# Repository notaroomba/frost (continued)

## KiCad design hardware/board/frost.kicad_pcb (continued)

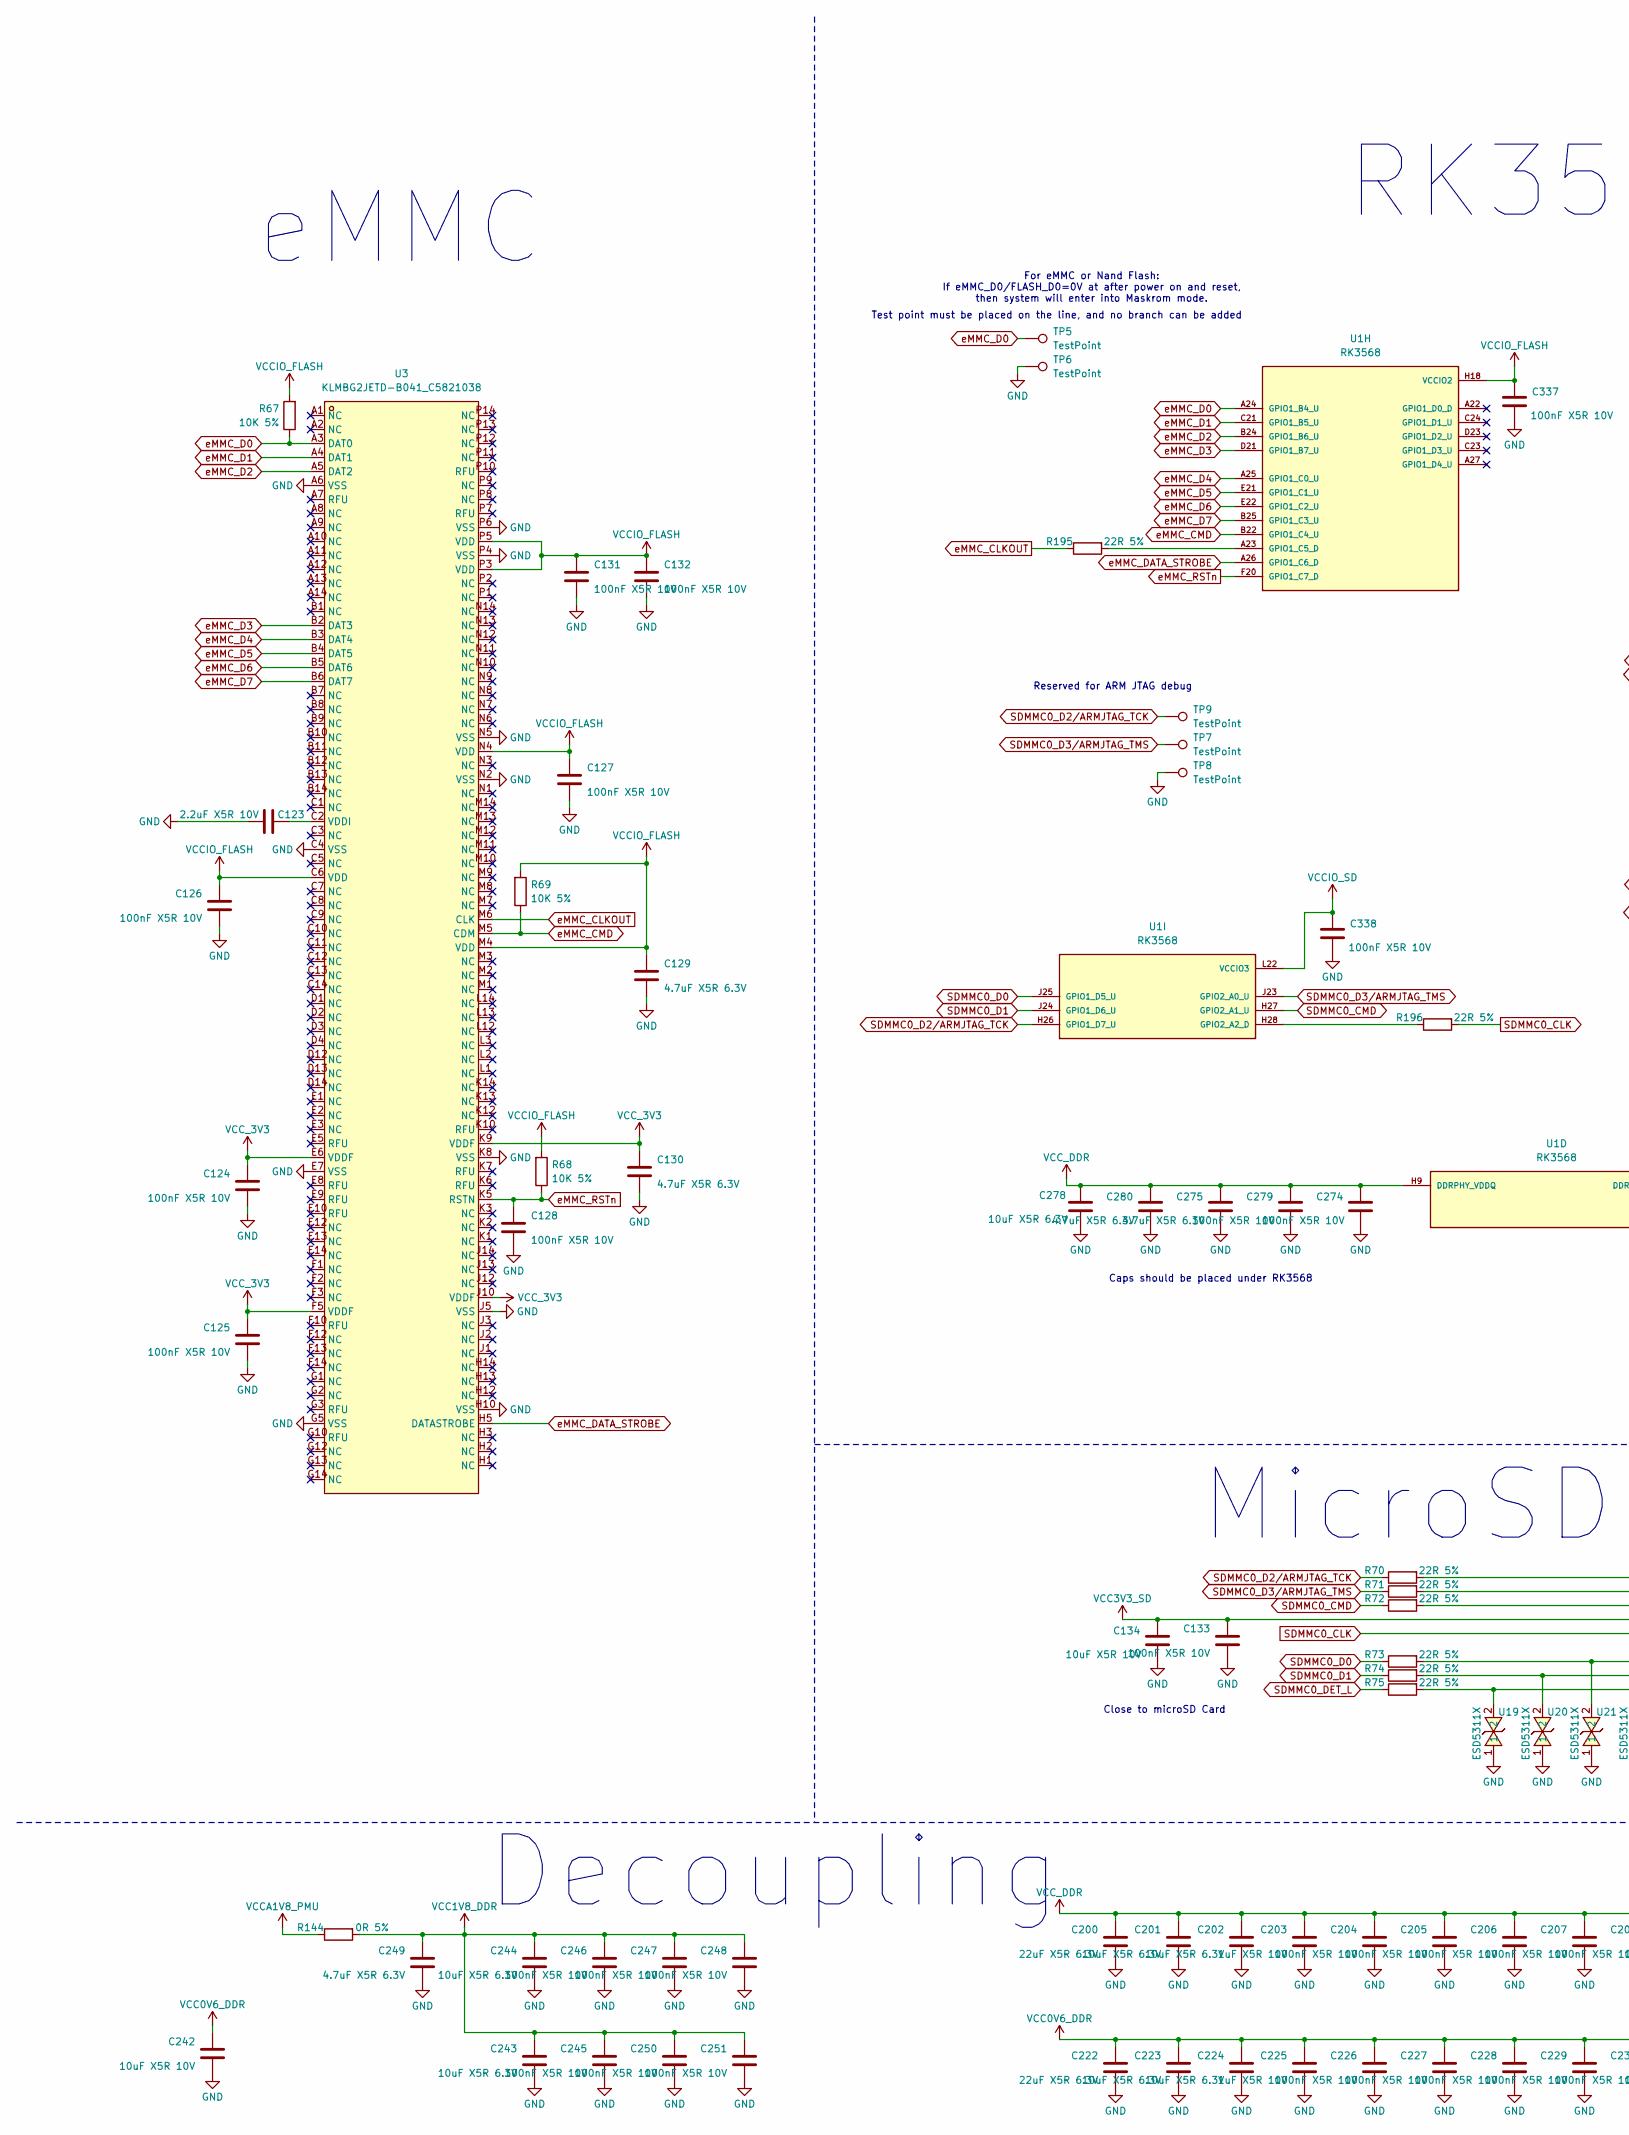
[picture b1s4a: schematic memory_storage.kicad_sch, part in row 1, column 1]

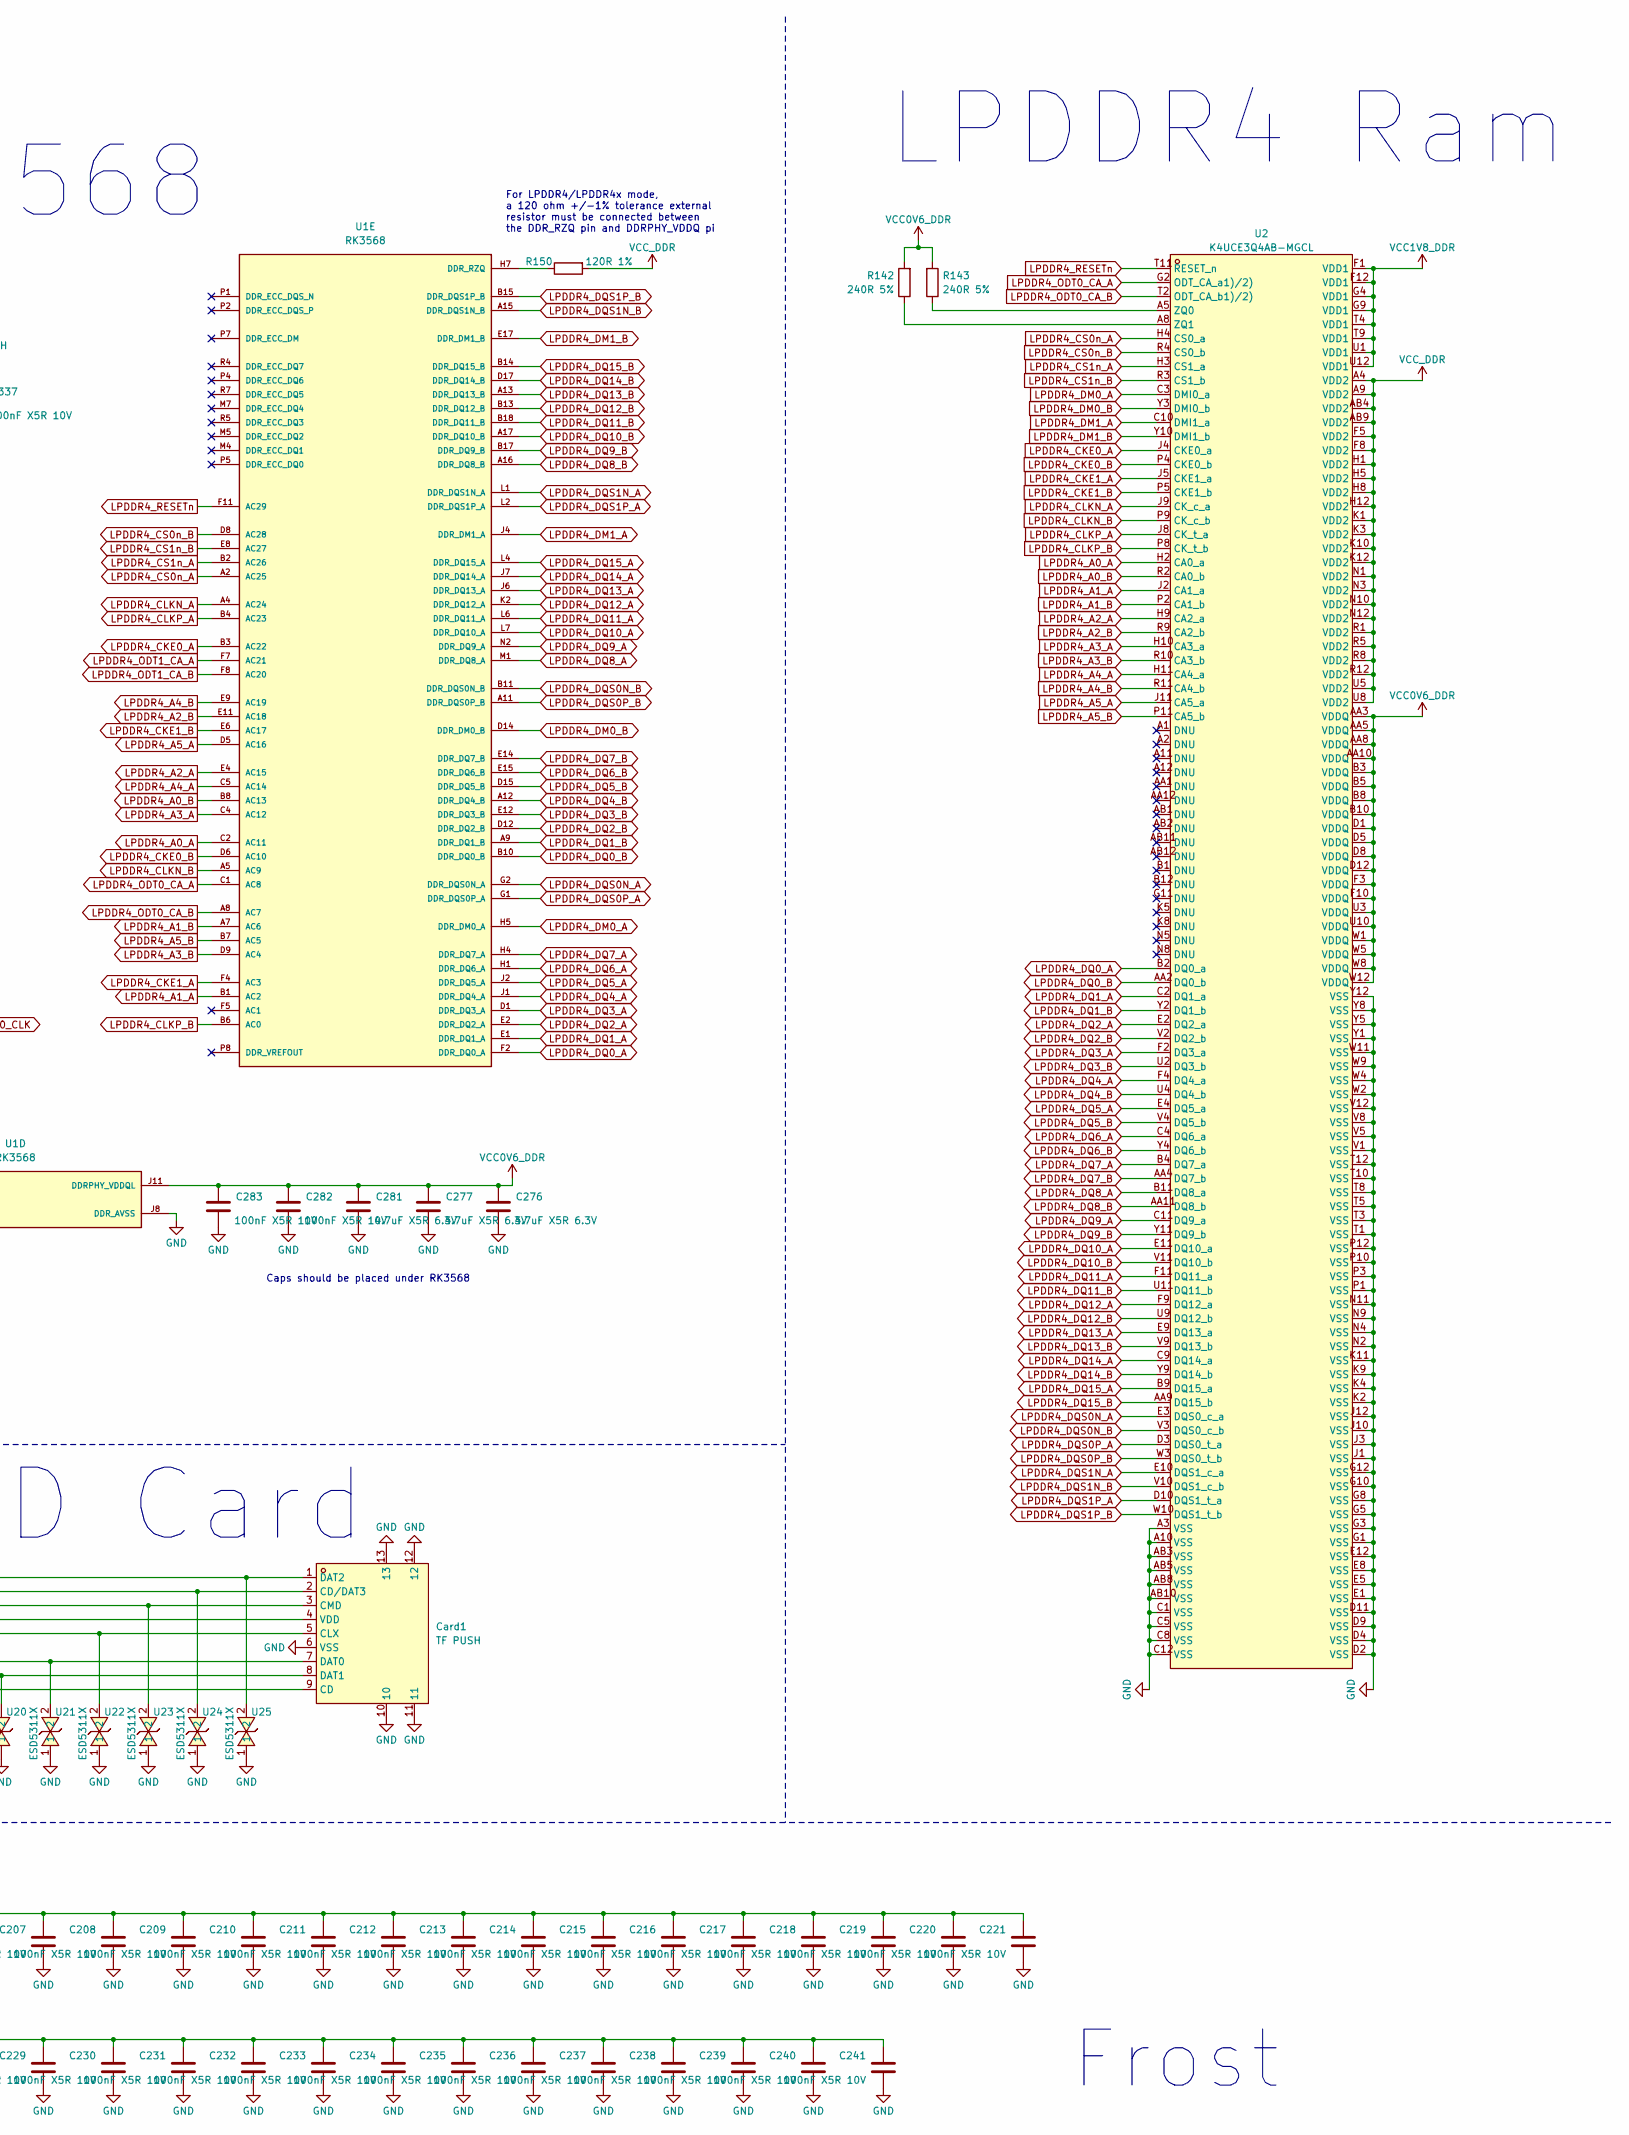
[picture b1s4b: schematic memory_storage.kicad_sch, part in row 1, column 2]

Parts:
C123: 2.2uF X5R 10V; C_0402_1005Metric
C124, C125, C126, C127, C128, C131, C132, C133, C204, C205, C206, C207, C208, C209, C210, C211, C212, C213, C214, C215, C216, C217, C218, C219, C220, C221, C226, C227, C228, C229, C230, C231, C232, C233, C234, C235, C236, C237, C238, C239, C240, C241, C245, C246, C247, C248, C250, C251: 100nF X5R 10V; C_0402_1005Metric
C129, C130: 4.7uF X5R 6.3V; C_0603_1608Metric
C134, C242: 10uF X5R 10V; C_0603_1608Metric
C200, C222: 22uF X5R 6.3V; C_0603_1608Metric
C201, C202, C223, C224, C243, C244, C278: 10uF X5R 6.3V; C_0603_1608Metric
C203, C225: 1uF X5R 10V; C_0402_1005Metric
C249, C275, C276, C277, C280, C281: 4.7uF X5R 6.3V; C_0402_1005Metric
C274, C279, C282, C283, C337, C338: 100nF X5R 10V; C_0201_0603Metric
Card1: TF PUSH; TF-SMD_TF-PUSH; LCSC Part C393941
R67, R68, R69: 10K 5%; R_0402_1005Metric
R70, R71, R72, R73, R74, R75, R195, R196: 22R 5%; R_0402_1005Metric
R142, R143: 240R 5%; R_0402_1005Metric
R144: 0R 5%; R_0201_0603Metric
R150: 120R 1%; R_0201_0603Metric
TP5, TP6, TP7, TP8, TP9: TestPoint; TestPoint_Pad_D1.0mm
U1: RK3568; BGA636C65P28X28_1900X1900X168; PARTREV 1.3; LCSC C3345225
U2: K4UCE3Q4AB-MGCL; FBGA-200_L15.0-W10.0-BL_RS512M32LO4D1BDS-53BT; LCSC Part C29073172
U3: KLMBG2JETD-B041_C5821038; BGA-153_L13.0-W11.5-P0.50-TL_KLM8G1GEME-B041; LCSC Part C5821038
U19, U20, U21, U22, U23, U24, U25: ESD5311X; DFN1006-2L-BI; LCSC Part C2844730

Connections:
LPDDR4_A0_A: U1.C2 (AC11), U2.H2 (CA0_a)
LPDDR4_A0_B: U1.B8 (AC13), U2.R2 (CA0_b)
LPDDR4_A1_A: U1.B1 (AC2), U2.J2 (CA1_a)
LPDDR4_A1_B: U1.A7 (AC6), U2.P2 (CA1_b)
LPDDR4_A2_A: U1.E4 (AC15), U2.H9 (CA2_a)
LPDDR4_A2_B: U1.E11 (AC18), U2.R9 (CA2_b)
LPDDR4_A3_A: U1.C4 (AC12), U2.H10 (CA3_a)
LPDDR4_A3_B: U1.D9 (AC4), U2.R10 (CA3_b)
LPDDR4_A4_A: U1.C5 (AC14), U2.H11 (CA4_a)
LPDDR4_A4_B: U1.E9 (AC19), U2.R11 (CA4_b)
LPDDR4_A5_A: U1.D5 (AC16), U2.J11 (CA5_a)
LPDDR4_A5_B: U1.B7 (AC5), U2.P11 (CA5_b)
LPDDR4_CKE0_A: U1.B3 (AC22), U2.J4 (CKE0_a)
LPDDR4_CKE0_B: U1.D6 (AC10), U2.P4 (CKE0_b)
LPDDR4_CKE1_A: U1.F4 (AC3), U2.J5 (CKE1_a)
LPDDR4_CKE1_B: U1.E6 (AC17), U2.P5 (CKE1_b)
LPDDR4_CLKN_A: U1.A4 (AC24), U2.J9 (CK_c_a)
LPDDR4_CLKN_B: U1.A5 (AC9), U2.P9 (CK_c_b)
LPDDR4_CLKP_A: U1.B4 (AC23), U2.J8 (CK_t_a)
LPDDR4_CLKP_B: U1.B6 (AC0), U2.P8 (CK_t_b)
LPDDR4_CS0n_A: U1.A2 (AC25), U2.H4 (CS0_a)
LPDDR4_CS0n_B: U1.D8 (AC28), U2.R4 (CS0_b)
LPDDR4_CS1n_A: U1.B2 (AC26), U2.H3 (CS1_a)
LPDDR4_CS1n_B: U1.E8 (AC27), U2.R3 (CS1_b)
LPDDR4_DM0_A: U1.H5 (DDR_DM0_A), U2.C3 (DMI0_a)
LPDDR4_DM0_B: U1.D14 (DDR_DM0_B), U2.Y3 (DMI0_b)
LPDDR4_DM1_A: U1.J4 (DDR_DM1_A), U2.C10 (DMI1_a)
LPDDR4_DM1_B: U1.E17 (DDR_DM1_B), U2.Y10 (DMI1_b)
LPDDR4_DQ0_A: U1.F2 (DDR_DQ0_A), U2.B2 (DQ0_a)
LPDDR4_DQ0_B: U1.B10 (DDR_DQ0_B), U2.AA2 (DQ0_b)
LPDDR4_DQ1_A: U1.E1 (DDR_DQ1_A), U2.C2 (DQ1_a)
LPDDR4_DQ1_B: U1.A9 (DDR_DQ1_B), U2.Y2 (DQ1_b)
LPDDR4_DQ2_A: U1.E2 (DDR_DQ2_A), U2.E2 (DQ2_a)
LPDDR4_DQ2_B: U1.D12 (DDR_DQ2_B), U2.V2 (DQ2_b)
LPDDR4_DQ3_A: U1.D1 (DDR_DQ3_A), U2.F2 (DQ3_a)
LPDDR4_DQ3_B: U1.E12 (DDR_DQ3_B), U2.U2 (DQ3_b)
LPDDR4_DQ4_A: U1.J1 (DDR_DQ4_A), U2.F4 (DQ4_a)
LPDDR4_DQ4_B: U1.A12 (DDR_DQ4_B), U2.U4 (DQ4_b)
LPDDR4_DQ5_A: U1.J2 (DDR_DQ5_A), U2.E4 (DQ5_a)
LPDDR4_DQ5_B: U1.D15 (DDR_DQ5_B), U2.V4 (DQ5_b)
LPDDR4_DQ6_A: U1.H1 (DDR_DQ6_A), U2.C4 (DQ6_a)
LPDDR4_DQ6_B: U1.E15 (DDR_DQ6_B), U2.Y4 (DQ6_b)
LPDDR4_DQ7_A: U1.H4 (DDR_DQ7_A), U2.B4 (DQ7_a)
LPDDR4_DQ7_B: U1.E14 (DDR_DQ7_B), U2.AA4 (DQ7_b)
LPDDR4_DQ8_A: U1.M1 (DDR_DQ8_A), U2.B11 (DQ8_a)
LPDDR4_DQ8_B: U1.A16 (DDR_DQ8_B), U2.AA11 (DQ8_b)
LPDDR4_DQ9_A: U1.N2 (DDR_DQ9_A), U2.C11 (DQ9_a)
LPDDR4_DQ9_B: U1.B17 (DDR_DQ9_B), U2.Y11 (DQ9_b)
LPDDR4_DQ10_A: U1.L7 (DDR_DQ10_A), U2.E11 (DQ10_a)
LPDDR4_DQ10_B: U1.A17 (DDR_DQ10_B), U2.V11 (DQ10_b)
LPDDR4_DQ11_A: U1.L6 (DDR_DQ11_A), U2.F11 (DQ11_a)
LPDDR4_DQ11_B: U1.B18 (DDR_DQ11_B), U2.U11 (DQ11_b)
LPDDR4_DQ12_A: U1.K2 (DDR_DQ12_A), U2.F9 (DQ12_a)
LPDDR4_DQ12_B: U1.B13 (DDR_DQ12_B), U2.U9 (DQ12_b)
LPDDR4_DQ13_A: U1.J6 (DDR_DQ13_A), U2.E9 (DQ13_a)
LPDDR4_DQ13_B: U1.A13 (DDR_DQ13_B), U2.V9 (DQ13_b)
LPDDR4_DQ14_A: U1.J7 (DDR_DQ14_A), U2.C9 (DQ14_a)
LPDDR4_DQ14_B: U1.D17 (DDR_DQ14_B), U2.Y9 (DQ14_b)
LPDDR4_DQ15_A: U1.L4 (DDR_DQ15_A), U2.B9 (DQ15_a)
LPDDR4_DQ15_B: U1.B14 (DDR_DQ15_B), U2.AA9 (DQ15_b)
LPDDR4_DQS0N_A: U1.G2 (DDR_DQS0N_A), U2.E3 (DQS0_c_a)
LPDDR4_DQS0N_B: U1.B11 (DDR_DQS0N_B), U2.V3 (DQS0_c_b)
LPDDR4_DQS0P_A: U1.G1 (DDR_DQS0P_A), U2.D3 (DQS0_t_a)
LPDDR4_DQS0P_B: U1.A11 (DDR_DQS0P_B), U2.W3 (DQS0_t_b)
LPDDR4_DQS1N_A: U1.L1 (DDR_DQS1N_A), U2.E10 (DQS1_c_a)
LPDDR4_DQS1N_B: U1.A15 (DDR_DQS1N_B), U2.V10 (DQS1_c_b)
LPDDR4_DQS1P_A: U1.L2 (DDR_DQS1P_A), U2.D10 (DQS1_t_a)
LPDDR4_DQS1P_B: U1.B15 (DDR_DQS1P_B), U2.W10 (DQS1_t_b)
LPDDR4_ODT0_CA_A: U1.C1 (AC8), U2.G2 (ODT_CA_a1)/2))
LPDDR4_ODT0_CA_B: U1.A8 (AC7), U2.T2 (ODT_CA_b1)/2))
LPDDR4_ODT1_CA_A: U1.F7 (AC21)
LPDDR4_ODT1_CA_B: U1.F8 (AC20)
LPDDR4_RESETn: U1.F11 (AC29), U2.T11 (RESET_n)
unnamed: Card1.9 (CD), R75.2, U19.2
unnamed: Card1.2 (CD/DAT3), R71.2, U24.2
unnamed: Card1.3 (CMD), R72.2, U23.2
unnamed: Card1.7 (DAT0), R73.2, U21.2
unnamed: Card1.8 (DAT1), R74.2, U20.2
unnamed: Card1.1 (DAT2), R70.2, U25.2
unnamed: R150.1, U1.H7 (DDR_RZQ)
unnamed: R195.2, U1.A23 (GPIO1_C5_D)
unnamed: R196.1, U1.H28 (GPIO2_A2_D)
unnamed: R143.1, U2.A5 (ZQ0)
unnamed: R142.1, U2.A8 (ZQ1)
unnamed: C123.1, U3.C2 (VDDI)
SDMMC0_CLK: Card1.5 (CLX), R196.2, U22.2
SDMMC0_CMD: R72.1, U1.H27 (GPIO2_A1_U)
SDMMC0_D0: R73.1, U1.J25 (GPIO1_D5_U)
SDMMC0_D1: R74.1, U1.J24 (GPIO1_D6_U)
SDMMC0_D2/ARMJTAG_TCK: R70.1, TP9.1, U1.H26 (GPIO1_D7_U)
SDMMC0_D3/ARMJTAG_TMS: R71.1, TP7.1, U1.J23 (GPIO2_A0_U)
SDMMC0_DET_L: R75.1; also elsewhere on the board
VCC0V6_DDR: C222.1, C223.1, C224.1, C225.1, C226.1, C227.1, C228.1, C229.1, C230.1, C231.1, C232.1, C233.1, C234.1, C235.1, C236.1, C237.1, C238.1, C239.1, C240.1, C241.1, C242.1, C276.1, C277.1, C281.1, C282.1, C283.1, R142.2, R143.2, U1.J11 (DDRPHY_VDDQL), U1.J12 (DDRPHY_VDDQL), U1.J14 (DDRPHY_VDDQL), U1.K10 (DDRPHY_VDDQL), U1.L10 (DDRPHY_VDDQL), U1.M10 (DDRPHY_VDDQL), U2.AA3 (VDDQ), U2.AA5 (VDDQ), U2.AA8 (VDDQ), U2.AA10 (VDDQ), U2.B3 (VDDQ), U2.B5 (VDDQ), U2.B8 (VDDQ), U2.B10 (VDDQ), U2.D1 (VDDQ), U2.D5 (VDDQ), U2.D8 (VDDQ), U2.D12 (VDDQ), U2.F3 (VDDQ), U2.F10 (VDDQ), U2.U3 (VDDQ), U2.U10 (VDDQ), U2.W1 (VDDQ), U2.W5 (VDDQ), U2.W8 (VDDQ), U2.W12 (VDDQ)
VCC1V8_DDR: C243.1, C244.1, C245.1, C246.1, C247.1, C248.1, C249.1, C250.1, C251.1, R144.2, U2.F1 (VDD1), U2.F12 (VDD1), U2.G4 (VDD1), U2.G9 (VDD1), U2.T4 (VDD1), U2.T9 (VDD1), U2.U1 (VDD1), U2.U12 (VDD1)
VCC3V3_SD: C133.1, C134.1, Card1.4 (VDD); also elsewhere on the board
VCCA1V8_PMU: R144.1; also elsewhere on the board
VCCIO_FLASH: C126.1, C127.1, C129.1, C131.1, C132.1, C337.1, R67.2, R68.2, R69.2, U1.H18 (VCCIO2), U3.C6 (VDD), U3.M4 (VDD), U3.N4 (VDD), U3.P3 (VDD), U3.P5 (VDD); also elsewhere on the board
VCCIO_SD: C338.1, U1.L22 (VCCIO3); also elsewhere on the board
VCC_3V3: C124.1, C125.1, C130.1, U3.E6 (VDDF), U3.F5 (VDDF), U3.J10 (VDDF), U3.K9 (VDDF); also elsewhere on the board
VCC_DDR: C200.1, C201.1, C202.1, C203.1, C204.1, C205.1, C206.1, C207.1, C208.1, C209.1, C210.1, C211.1, C212.1, C213.1, C214.1, C215.1, C216.1, C217.1, C218.1, C219.1, C220.1, C221.1, C274.1, C275.1, C278.1, C279.1, C280.1, R150.2, U1.H9 (DDRPHY_VDDQ), U1.H11 (DDRPHY_VDDQ), U1.H12 (DDRPHY_VDDQ), U1.H14 (DDRPHY_VDDQ), U1.H15 (DDRPHY_VDDQ), U1.J9 (DDRPHY_VDDQ), U1.L9 (DDRPHY_VDDQ), U1.M9 (DDRPHY_VDDQ), U2.A4 (VDD2), U2.A9 (VDD2), U2.AB4 (VDD2), U2.AB9 (VDD2), U2.F5 (VDD2), U2.F8 (VDD2), U2.H1 (VDD2), U2.H5 (VDD2), U2.H8 (VDD2), U2.H12 (VDD2), U2.K1 (VDD2), U2.K3 (VDD2), U2.K10 (VDD2), U2.K12 (VDD2), U2.N1 (VDD2), U2.N3 (VDD2), U2.N10 (VDD2), U2.N12 (VDD2), U2.R1 (VDD2), U2.R5 (VDD2), U2.R8 (VDD2), U2.R12 (VDD2), U2.U5 (VDD2), U2.U8 (VDD2); also elsewhere on the board
eMMC_CLKOUT: R195.1, U3.M6 (CLK)
eMMC_CMD: R69.1, U1.B22 (GPIO1_C4_U), U3.M5 (CDM)
eMMC_D0: R67.1, TP5.1, U1.A24 (GPIO1_B4_U), U3.A3 (DAT0)
eMMC_D1: U1.C21 (GPIO1_B5_U), U3.A4 (DAT1)
eMMC_D2: U1.B24 (GPIO1_B6_U), U3.A5 (DAT2)
eMMC_D3: U1.D21 (GPIO1_B7_U), U3.B2 (DAT3)
eMMC_D4: U1.A25 (GPIO1_C0_U), U3.B3 (DAT4)
eMMC_D5: U1.E21 (GPIO1_C1_U), U3.B4 (DAT5)
eMMC_D6: U1.E22 (GPIO1_C2_U), U3.B5 (DAT6)
eMMC_D7: U1.B25 (GPIO1_C3_U), U3.B6 (DAT7)
eMMC_DATA_STROBE: U1.A26 (GPIO1_C6_D), U3.H5 (DATASTROBE)
eMMC_RSTn: C128.1, R68.1, U1.F20 (GPIO1_C7_D), U3.K5 (RSTN)

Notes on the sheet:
Caps should be placed under RK3568
Test point must be placed on the line, and no branch can be added
LPDDR4 Ram
Reserved for ARM JTAG debug
Close to microSD Card
Decoupling
For LPDDR4/LPDDR4x mode, a 120 ohm +/-1% tolerance external resistor must be connected between the DDR_RZQ pin and DDRPHY_VDDQ pi
For eMMC or Nand Flash: If eMMC_D0/FLASH_D0=0V at after power on and reset, then system will enter into Maskrom mode.
eMMC
MicroSD Card
Frost
RK3568

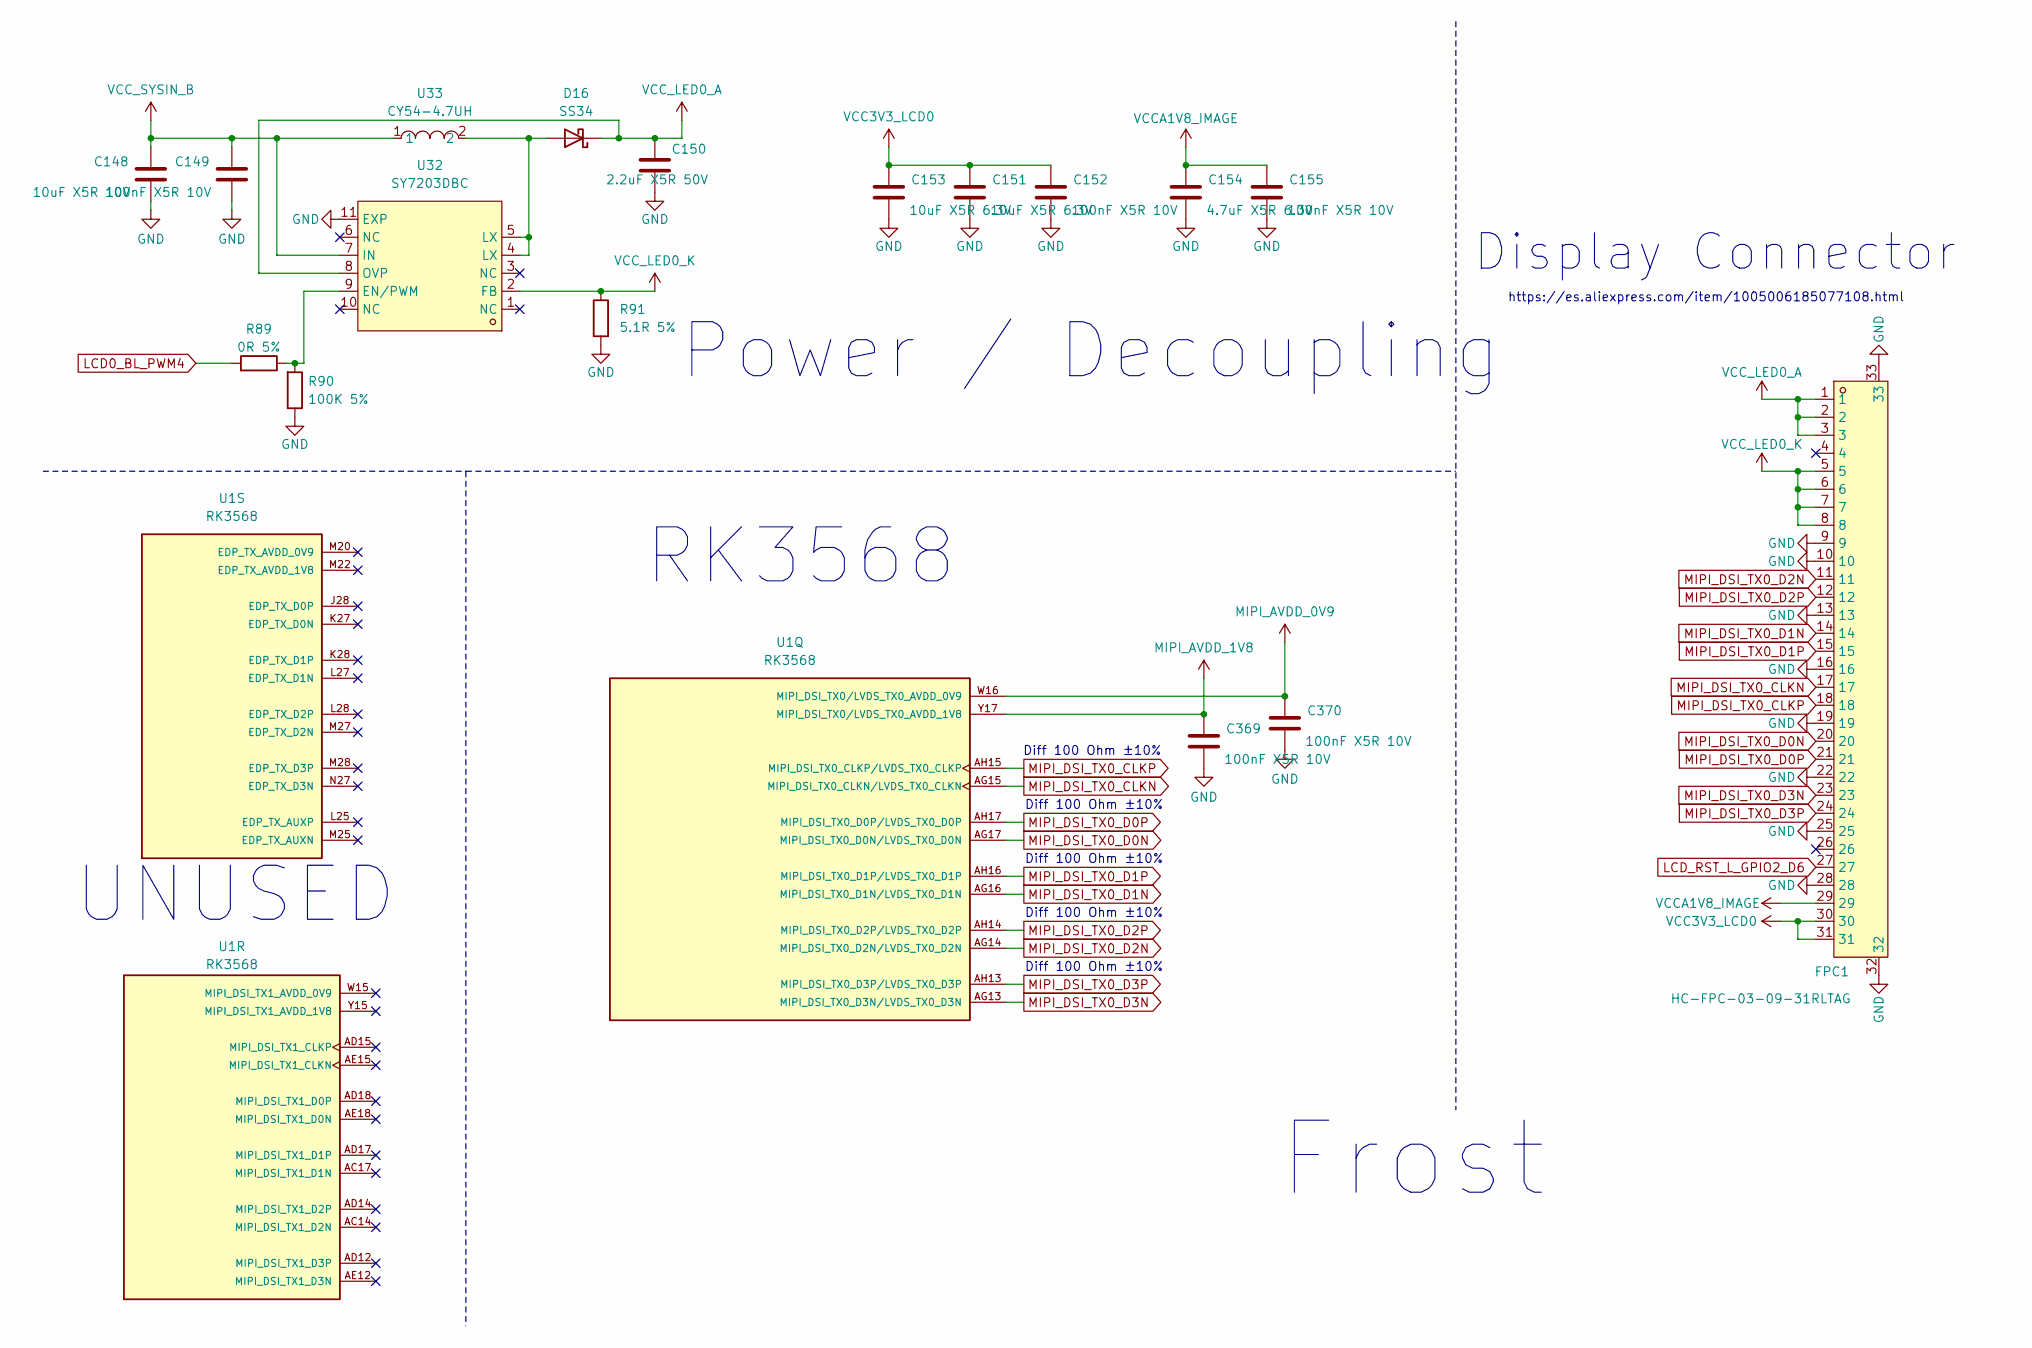
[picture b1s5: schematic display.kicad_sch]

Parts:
C148: 10uF X5R 10V; C_0603_1608Metric
C149, C152, C155: 100nF X5R 10V; C_0402_1005Metric
C150: 2.2uF X5R 50V; C_0805_2012Metric
C151, C153: 10uF X5R 6.3V; C_0603_1608Metric
C154: 4.7uF X5R 6.3V; C_0603_1608Metric
C369, C370: 100nF X5R 10V; C_0201_0603Metric
D16: SS34; D_SMA
FPC1: HC-FPC-03-09-31RLTAG; FPC-SMD_31P-P0.30_HC-FPC-03-09-31RLTAG; LCSC Part C5213720
R89: 0R 5%; R_0402_1005Metric
R90: 100K 5%; R_0402_1005Metric
R91: 5.1R 5%; R_1206_3216Metric
U1: RK3568; BGA636C65P28X28_1900X1900X168; PARTREV 1.3; LCSC C3345225
U32: SY7203DBC; DFN-10_L3.0-W3.0-P0.50-BL-EP2.4; LCSC Part C125894
U33: CY54-4.7UH; IND-SMD_L5.8-W5.2; LCSC Part C2929429

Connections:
LCD0_BL_PWM4: R89.2; also elsewhere on the board
LCD_RST_L_GPIO2_D6: FPC1.27; also elsewhere on the board
MIPI_AVDD_0V9: C370.1, U1.W16 (MIPI_DSI_TX0/LVDS_TX0_AVDD_0V9); also elsewhere on the board
MIPI_AVDD_1V8: C369.1, U1.Y17 (MIPI_DSI_TX0/LVDS_TX0_AVDD_1V8); also elsewhere on the board
MIPI_DSI_TX0_CLKN: FPC1.17, U1.AG15 (MIPI_DSI_TX0_CLKN/LVDS_TX0_CLKN)
MIPI_DSI_TX0_CLKP: FPC1.18, U1.AH15 (MIPI_DSI_TX0_CLKP/LVDS_TX0_CLKP)
MIPI_DSI_TX0_D0N: FPC1.20, U1.AG17 (MIPI_DSI_TX0_D0N/LVDS_TX0_D0N)
MIPI_DSI_TX0_D0P: FPC1.21, U1.AH17 (MIPI_DSI_TX0_D0P/LVDS_TX0_D0P)
MIPI_DSI_TX0_D1N: FPC1.14, U1.AG16 (MIPI_DSI_TX0_D1N/LVDS_TX0_D1N)
MIPI_DSI_TX0_D1P: FPC1.15, U1.AH16 (MIPI_DSI_TX0_D1P/LVDS_TX0_D1P)
MIPI_DSI_TX0_D2N: FPC1.11, U1.AG14 (MIPI_DSI_TX0_D2N/LVDS_TX0_D2N)
MIPI_DSI_TX0_D2P: FPC1.12, U1.AH14 (MIPI_DSI_TX0_D2P/LVDS_TX0_D2P)
MIPI_DSI_TX0_D3N: FPC1.23, U1.AG13 (MIPI_DSI_TX0_D3N/LVDS_TX0_D3N)
MIPI_DSI_TX0_D3P: FPC1.24, U1.AH13 (MIPI_DSI_TX0_D3P/LVDS_TX0_D3P)
unnamed: D16.2 (A), U32.4 (LX), U32.5 (LX), U33.2
unnamed: R89.1, R90.2, U32.9 (EN/PWM)
VCC3V3_LCD0: C151.1, C152.1, C153.1, FPC1.30, FPC1.31; also elsewhere on the board
VCCA1V8_IMAGE: C154.1, C155.1, FPC1.29; also elsewhere on the board
VCC_LED0_A: C150.1, D16.1 (K), FPC1.1, FPC1.2, FPC1.3, U32.8 (OVP)
VCC_LED0_K: FPC1.5, FPC1.6, FPC1.7, FPC1.8, R91.1, U32.2 (FB)
VCC_SYSIN: C148.1, C149.1, U32.7 (IN), U33.1; also elsewhere on the board

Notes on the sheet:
Diff 100 Ohm ±10%
Frost
RK3568
Power / Decoupling
Display Connector
UNUSED
https://es.aliexpress.com/item/1005006185077108.html

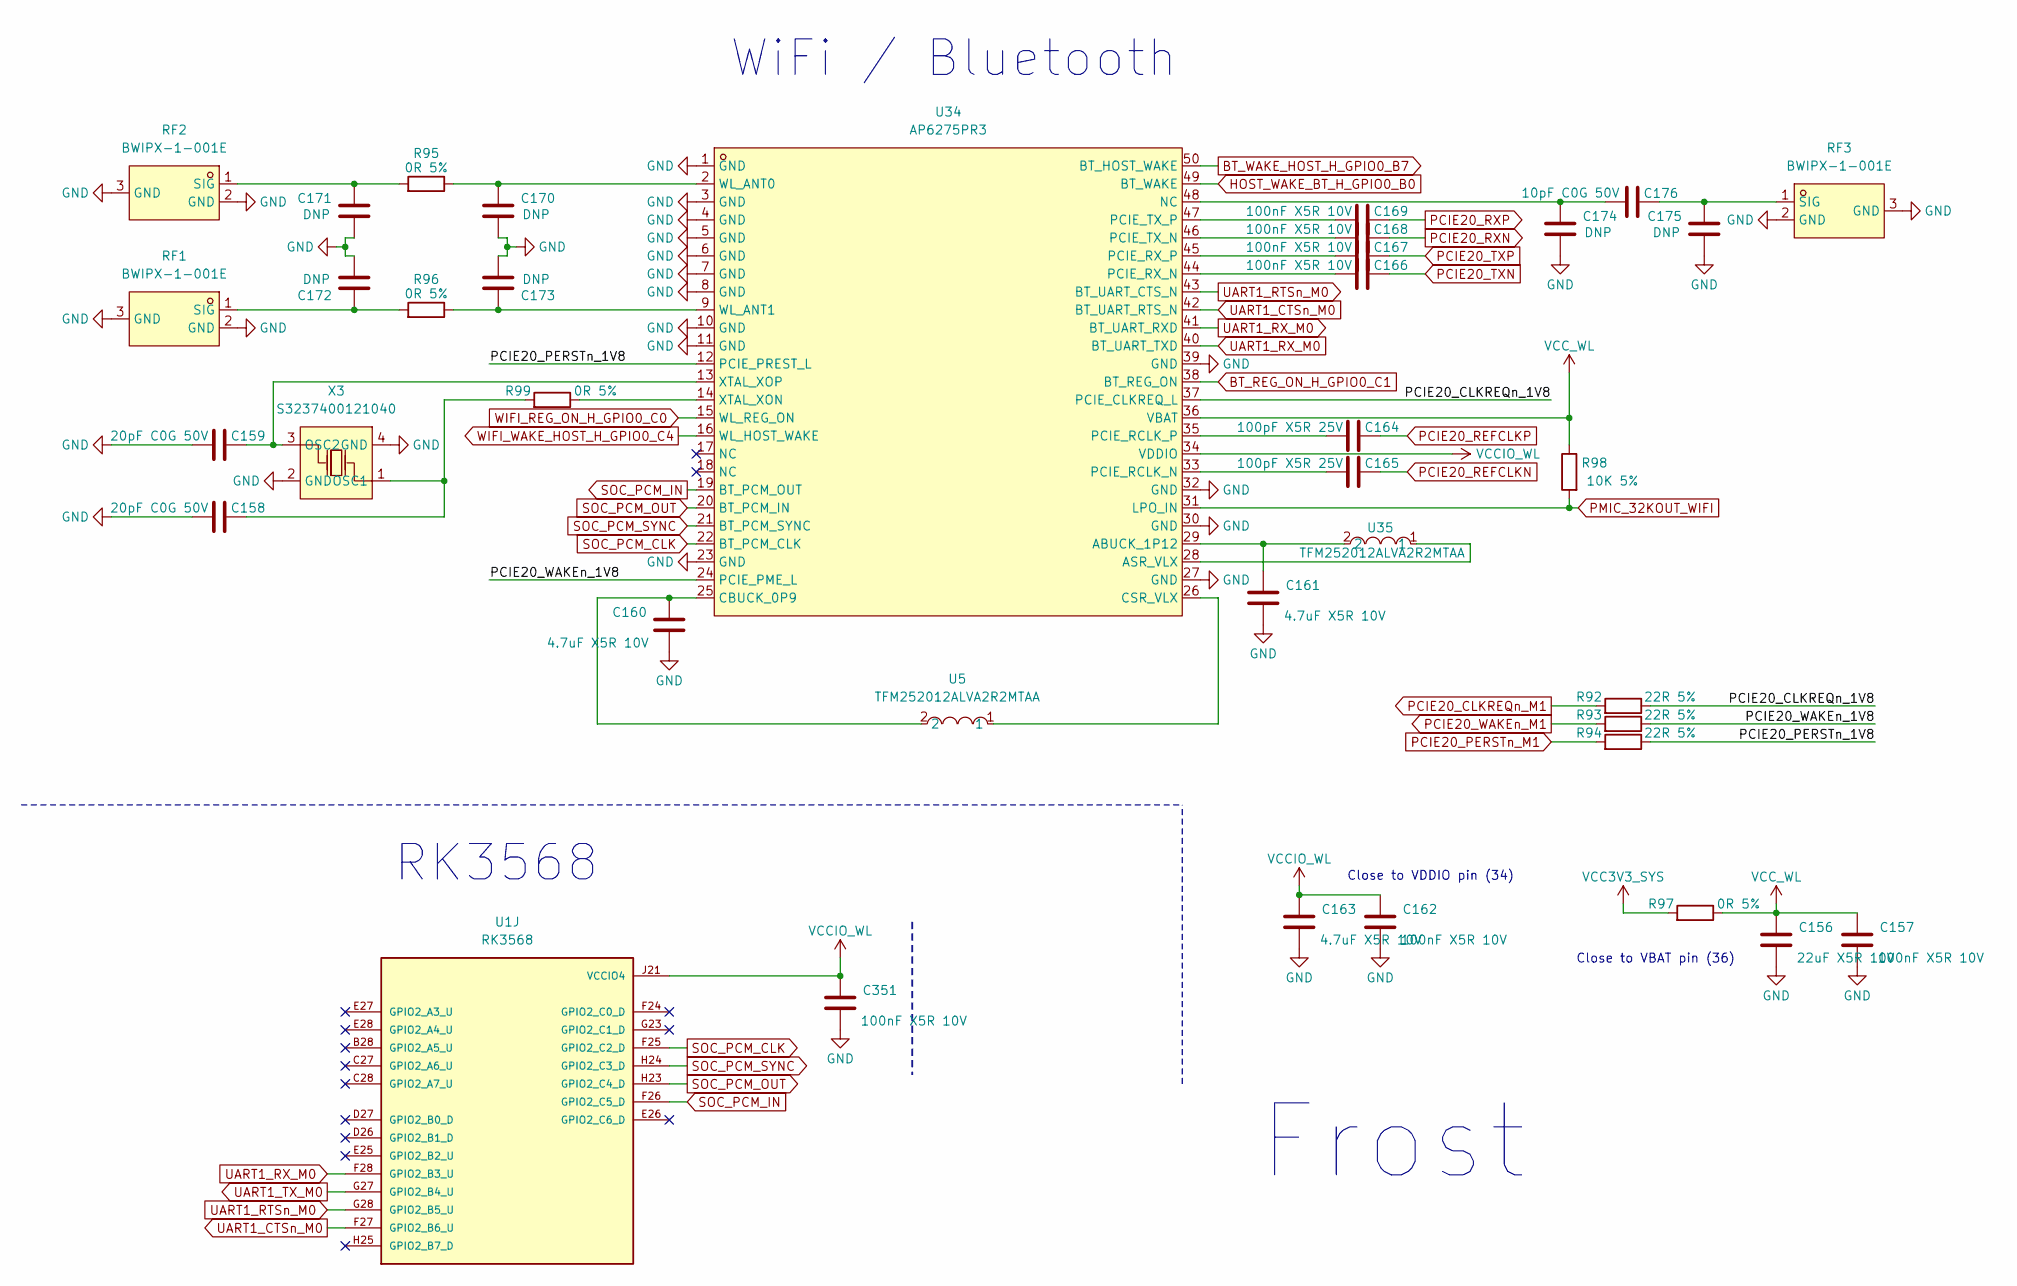
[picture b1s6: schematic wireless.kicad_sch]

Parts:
C156: 22uF X5R 10V; C_0805_2012Metric
C157, C162: 100nF X5R 10V; C_0402_1005Metric
C158, C159: 20pF C0G 50V; C_0402_1005Metric
C160, C161, C163: 4.7uF X5R 10V; C_0603_1608Metric
C164, C165: 100pF X5R 25V; C_0201_0603Metric
C166, C167, C168, C169, C351: 100nF X5R 10V; C_0201_0603Metric
C170, C171, C172, C173, C174, C175: DNP; C_0402_1005Metric
C176: 10pF C0G 50V; C_0201_0603Metric
R92, R93, R94: 22R 5%; R_0402_1005Metric
R95, R96, R97: 0R 5%; R_0603_1608Metric
R98: 10K 5%; R_0402_1005Metric
R99: 0R 5%; R_0402_1005Metric
RF1, RF2, RF3: BWIPX-1-001E; IPEX-SMD_BWIPX-1-001E; LCSC Part C496552
U1: RK3568; BGA636C65P28X28_1900X1900X168; PARTREV 1.3; LCSC C3345225
U5, U35: TFM252012ALVA2R2MTAA; L1008; LCSC Part C2047711
U34: AP6275PR3; WIRELM-SMD_AMPAK_AP6275P; LCSC Part C2984106
X3: S3237400121040; CRYSTAL-SMD_4P-L3.2-W2.5-BL; LCSC Part C426987

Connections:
/WiFi and Bluetooth/PCIE20_CLKREQn_1V8: R92.1, U34.37 (PCIE_CLKREQ_L)
/WiFi and Bluetooth/PCIE20_PERSTn_1V8: R94.1, U34.12 (PCIE_PREST_L)
/WiFi and Bluetooth/PCIE20_WAKEn_1V8: R93.1, U34.24 (PCIE_PME_L)
BT_REG_ON_H_GPIO0_C1: U34.38 (BT_REG_ON); also elsewhere on the board
BT_WAKE_HOST_H_GPIO0_B7: U34.50 (BT_HOST_WAKE); also elsewhere on the board
HOST_WAKE_BT_H_GPIO0_B0: U34.49 (BT_WAKE); also elsewhere on the board
unnamed: C174.1, C176.2, U34.48 (NC)
unnamed: C172.1, R96.2, RF1.1 (SIG)
unnamed: C171.1, R95.2, RF2.1 (SIG)
unnamed: C175.1, C176.1, RF3.1 (SIG)
unnamed: C161.1, U34.29 (ABUCK_1P12), U35.2
unnamed: U34.28 (ASR_VLX), U35.1
unnamed: C160.1, U5.2, U34.25 (CBUCK_0P9)
unnamed: U5.1, U34.26 (CSR_VLX)
unnamed: C165.2, U34.33 (PCIE_RCLK_N)
unnamed: C164.2, U34.35 (PCIE_RCLK_P)
unnamed: C166.2, U34.44 (PCIE_RX_N)
unnamed: C167.2, U34.45 (PCIE_RX_P)
unnamed: C168.2, U34.46 (PCIE_TX_N)
unnamed: C169.2, U34.47 (PCIE_TX_P)
unnamed: C170.1, R95.1, U34.2 (WL_ANT0)
unnamed: C173.1, R96.1, U34.9 (WL_ANT1)
unnamed: R99.1, U34.14 (XTAL_XON)
unnamed: C159.1, U34.13 (XTAL_XOP), X3.3 (OSC2)
unnamed: C158.1, R99.2, X3.1 (OSC1)
PCIE20_CLKREQn_M1: R92.2; also elsewhere on the board
PCIE20_PERSTn_M1: R94.2; also elsewhere on the board
PCIE20_REFCLKN: C165.1; also elsewhere on the board
PCIE20_REFCLKP: C164.1; also elsewhere on the board
PCIE20_RXN: C168.1; also elsewhere on the board
PCIE20_RXP: C169.1; also elsewhere on the board
PCIE20_TXN: C166.1; also elsewhere on the board
PCIE20_TXP: C167.1; also elsewhere on the board
PCIE20_WAKEn_M1: R93.2; also elsewhere on the board
PMIC_32KOUT_WIFI: R98.2, U34.31 (LPO_IN); also elsewhere on the board
SOC_PCM_CLK: U1.F25 (GPIO2_C2_D), U34.22 (BT_PCM_CLK)
SOC_PCM_IN: U1.F26 (GPIO2_C5_D), U34.19 (BT_PCM_OUT)
SOC_PCM_OUT: U1.H23 (GPIO2_C4_D), U34.20 (BT_PCM_IN)
SOC_PCM_SYNC: U1.H24 (GPIO2_C3_D), U34.21 (BT_PCM_SYNC)
UART1_CTSn_M0: U1.F27 (GPIO2_B6_U), U34.42 (BT_UART_RTS_N)
UART1_RTSn_M0: U1.G28 (GPIO2_B5_U), U34.43 (BT_UART_CTS_N)
UART1_RX_M0: U1.F28 (GPIO2_B3_U), U34.40 (BT_UART_TXD), U34.41 (BT_UART_RXD)
UART1_TX_M0: U1.G27 (GPIO2_B4_U)
VCC3V3_SYS: R97.2; also elsewhere on the board
VCCIO_WL: C162.1, C163.1, C351.1, U1.J21 (VCCIO4), U34.34 (VDDIO); also elsewhere on the board
VCC_WL: C156.1, C157.1, R97.1, R98.1, U34.36 (VBAT)
WIFI_REG_ON_H_GPIO0_C0: U34.15 (WL_REG_ON); also elsewhere on the board
WIFI_WAKE_HOST_H_GPIO0_C4: U34.16 (WL_HOST_WAKE); also elsewhere on the board

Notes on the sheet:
Close to VBAT pin (36)
WiFi / Bluetooth
Close to VDDIO pin (34)
Frost
RK3568
